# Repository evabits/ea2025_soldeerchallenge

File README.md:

# ea2025_soldeerchallenge

Hardware and Software for the soldering challenge of the Electronics and Automation fair 2025. The board includes an RP2040, a 5x5 neopixel LED array and a breakout connector. You can use it as an RP2040 development kit afterwards, starting with the Arduino file. Leave a note on our linkedin-page on how you've done. Good luck soldering!

## Important Notice  

Some Arduino board libraries may cause **GPIO pattern mismatches**.  

The only supported and correct board for running `FHI_SolderChallenge2025.ino` is:  

**Raspberry Pi Pico (RP2040) by Earle F. Philhower**

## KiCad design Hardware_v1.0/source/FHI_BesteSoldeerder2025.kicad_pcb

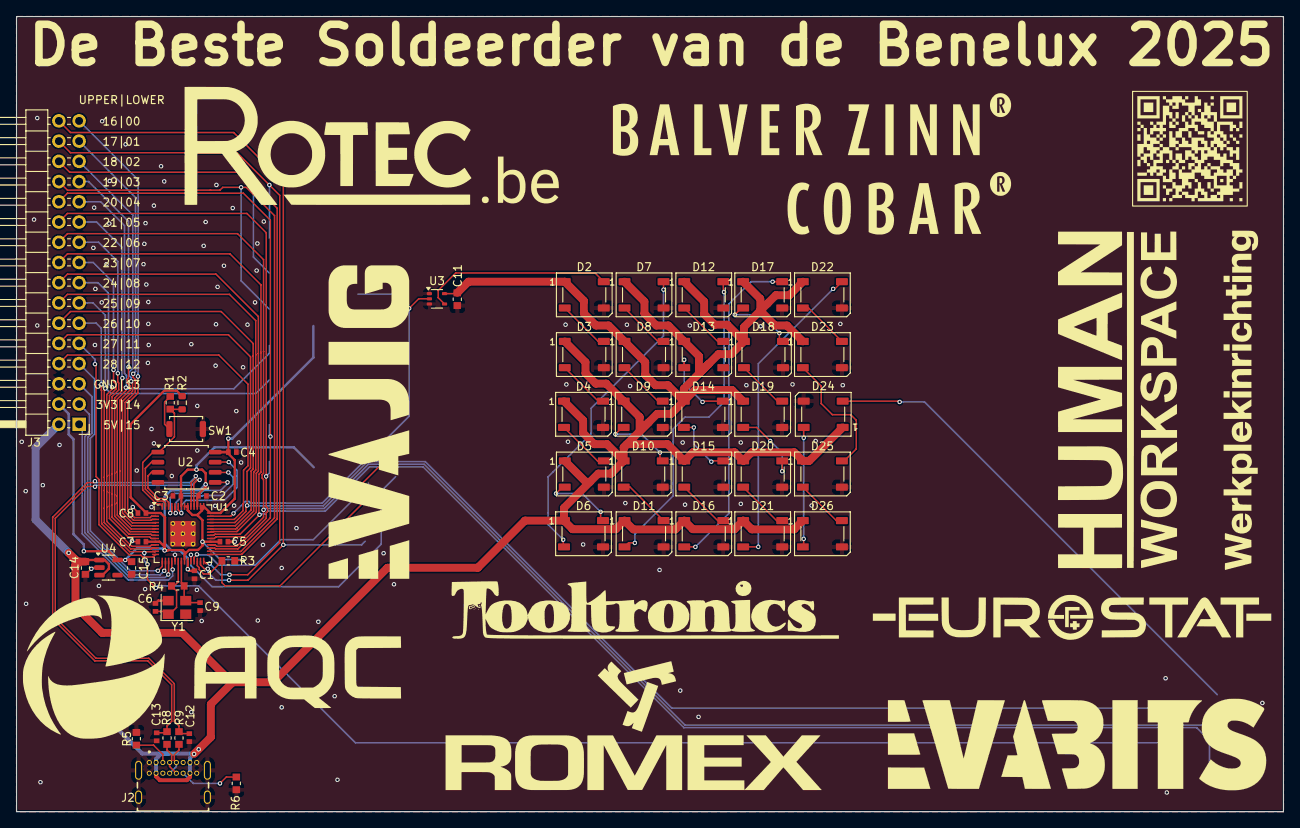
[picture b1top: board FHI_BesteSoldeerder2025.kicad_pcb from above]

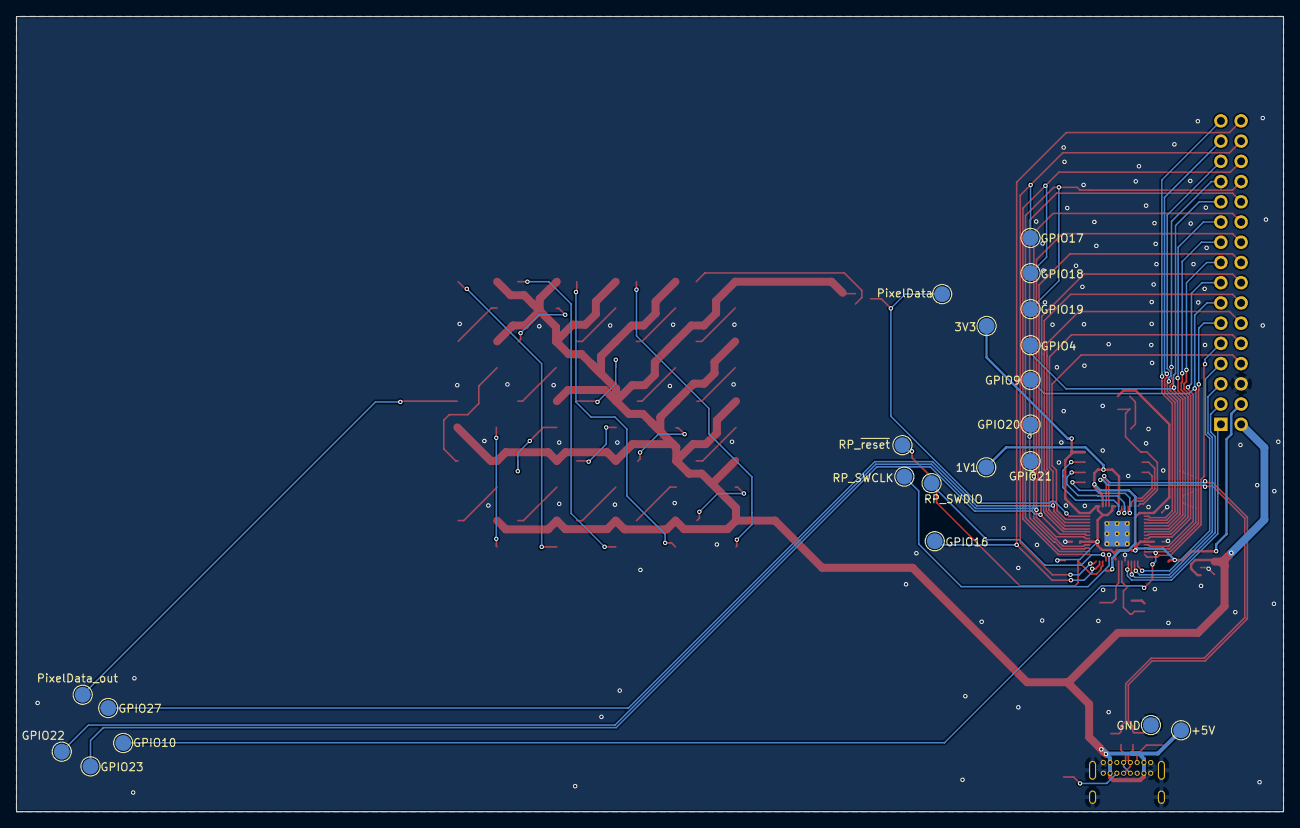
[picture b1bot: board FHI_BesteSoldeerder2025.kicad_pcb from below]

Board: 2 copper layers, 159.1 x 99.8 mm, 79 parts (21 on the bottom side), 78 nets.

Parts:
C1, C2, C3, C4, C5, C7, C8: 0.1uF; C_0402_1005Metric
C6, C9: 10pf; C_0402_1005Metric
C11, C14, C15: 1uF; C_0603_1608Metric
C12, C13: 22pF; C_0402_1005Metric
D2, D3, D4, D5, D6, D7, D8, D9, D10, D11, D12, D13, D14, D15, D16, D17, D18, D19, D20, D21, D22, D23, D24, D25, D26: WS2812B; LED_WS2812B_PLCC4_5.0x5.0mm_P3.2mm
J2: USB4085-GF-A_REVB; GCT_USB4085-GF-A_REVB
J3: Conn_02x16_Odd_Even; PinHeader_2x16_P2.54mm_Horizontal
R1: 1k5; R_0603_1608Metric
R2: DNP; R_0603_1608Metric
R3: 10K; R_0603_1608Metric
R4: 1M; R_0603_1608Metric
R5, R6: 5k1; R_0603_1608Metric
R8, R9: 27R; R_0603_1608Metric
SW1: SKRKAGE020; SW_Push_SPST_NO_Alps_SKRK
TP1: +5V; TestPoint_Pad_D1.5mm
TP3: GND; TestPoint_Pad_D1.5mm
TP28: GPIO27; TestPoint_Pad_D1.5mm
TP29: PixelData_out; TestPoint_Pad_D1.5mm
TP31: GPIO10; TestPoint_Pad_D1.5mm
TP32: GPIO22; TestPoint_Pad_D1.5mm
TP33: GPIO23; TestPoint_Pad_D1.5mm
TP55: GPIO21; TestPoint_Pad_D1.5mm
TP56: GPIO20; TestPoint_Pad_D1.5mm
TP57: GPIO9; TestPoint_Pad_D1.5mm
TP59: GPIO4; TestPoint_Pad_D1.5mm
TP60: GPIO19; TestPoint_Pad_D1.5mm
TP61: GPIO18; TestPoint_Pad_D1.5mm
TP62: GPIO17; TestPoint_Pad_D1.5mm
TP63: 1V1; TestPoint_Pad_D1.5mm
TP64: 3V3; TestPoint_Pad_D1.5mm
TP74: RP_SWDIO; TestPoint_Pad_D1.5mm
TP75: RP_~{reset}; TestPoint_Pad_D1.5mm
TP76: RP_SWCLK; TestPoint_Pad_D1.5mm
TP83: GPIO16; TestPoint_Pad_D1.5mm
TP84: PixelData; TestPoint_Pad_D1.5mm
U1: RP2040; QFN-56-1EP_7x7mm_P0.4mm_EP3.1x3.1mm_ThermalVias
U2: W25Q128JVSIQ; SOIC-8_5.23x5.23mm_P1.27mm
U3: 74HCT1G125GW; SOT-353_SC-70-5
U4: AP2112K-3.3V; TSOT-23-5
V1: QR-code; QRcode14mmx14mm
V2: EVAbits_logo; EVAbits_newlogo 48x12mm
V3: evajig_logo; evajig_logo_40x10
Y1: 12MHz,10pF; Crystal_SMD_3225-4Pin_3.2x2.5mm

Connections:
+3V3: C4.2, C5.2, C7.2, C8.2, C15.2, J3.4, R2.1, R3.2, TP64.1, U1.1 (IOVDD), U1.10 (IOVDD), U1.22 (IOVDD), U1.33 (IOVDD), U1.42 (IOVDD), U1.43 (ADC-AVDD), U1.44 (VREG-VIN), U1.48 (USB-VDD), U1.49 (IOVDD), U2.8 (VCC), U4.5 (OUT)
+5V: C11.2, C14.2, D2.1 (VDD), D3.1 (VDD), D4.1 (VDD), D5.1 (VDD), D6.1 (VDD), D7.1 (VDD), D8.1 (VDD), D9.1 (VDD), D10.1 (VDD), D11.1 (VDD), D12.1 (VDD), D13.1 (VDD), D14.1 (VDD), D15.1 (VDD), D16.1 (VDD), D17.1 (VDD), D18.1 (VDD), D19.1 (VDD), D20.1 (VDD), D21.1 (VDD), D22.1 (VDD), D23.1 (VDD), D24.1 (VDD), D25.1 (VDD), D26.1 (VDD), J2.A4 (VBUS), J2.A9 (VBUS), J2.B4 (VBUS), J2.B9 (VBUS), J3.2, TP1.1, U3.5 (Vcc), U4.1 (IN), U4.3 (EN)
/+1v1: C1.2, C2.2, C3.2, TP63.1, U1.23 (DVDD), U1.45 (VREG-VOUT), U1.50 (DVDD)
/GPIO00: J3.31, U1.2 (GPIO0)
/GPIO01: J3.29, U1.3 (GPIO1)
/GPIO02: J3.27, U1.4 (GPIO2)
/GPIO03: J3.25, U1.5 (GPIO3)
/GPIO04: J3.23, TP59.1, U1.6 (GPIO4)
/GPIO05: J3.21, U1.7 (GPIO5)
/GPIO06: J3.19, U1.8 (GPIO6)
/GPIO07: J3.17, U1.9 (GPIO7)
/GPIO08: J3.15, U1.11 (GPIO8)
/GPIO09: J3.13, TP57.1, U1.12 (GPIO9)
/GPIO10: J3.11, TP31.1, U1.13 (GPIO10)
/GPIO11: J3.9, U1.14 (GPIO11)
/GPIO12: J3.7, U1.15 (GPIO12)
/GPIO13: J3.5, U1.16 (GPIO13)
/GPIO14: J3.3, U1.17 (GPIO14)
/GPIO15: J3.1, U1.18 (GPIO15)
/GPIO16: J3.32, TP83.1, U1.27 (GPIO16)
/GPIO17: J3.30, TP62.1, U1.28 (GPIO17)
/GPIO18: J3.28, TP61.1, U1.29 (GPIO18)
/GPIO19: J3.26, TP60.1, U1.30 (GPIO19)
/GPIO20: J3.24, TP56.1, U1.31 (GPIO20)
/GPIO21: J3.22, TP55.1, U1.32 (GPIO21)
/GPIO22: J3.20, TP32.1, U1.34 (GPIO22)
/GPIO23: J3.18, TP33.1, U1.35 (GPIO23)
/GPIO24: J3.16, U1.36 (GPIO24)
/GPIO25: J3.14, U1.37 (GPIO25)
/GPIO26: J3.12, U1.38 (GPIO26/ADC0)
/GPIO27: J3.10, TP28.1, U1.39 (GPIO27/ADC1)
/GPIO28: J3.8, U1.40 (GPIO28/ADC2)
/NeoPixel_data: TP84.1, U1.41 (GPIO29/ADC3), U3.2 (A)
/NeoPixel_data_out: D24.2 (DOUT), TP29.1
/PICO_RESET: R3.1, TP75.1, U1.26 (RUN)
/PICO_TCKS: TP76.1, U1.24 (SWCLK)
/PICO_TMSS: TP74.1, U1.25 (SWDIO)
/QSPI_SCLK: U1.52 (QSPI-SCLK), U2.6 (CLK)
/QSPI_SD0: U1.53 (QSPI-SD0), U2.5 (DI(IO0))
/QSPI_SD1: U1.55 (QSPI-SD1), U2.2 (DO(IO1))
/QSPI_SD2: U1.54 (QSPI-SD2), U2.3 (IO2)
/QSPI_SD3: U1.51 (QSPI-SD3), U2.7 (IO3)
/QSPI_SS: R1.2, R2.2, U1.56 (QSPI-SS-N), U2.1 (~CS)
/USB_D+: C13.2, R8.1, U1.47 (USB-DP)
/USB_D-: C12.1, R9.1, U1.46 (USB-DM)
/USB_N: J2.A7 (DN1), J2.B7 (DN2), R9.2
/USB_P: J2.A6 (DP1), J2.B6 (DP2), R8.2
/~USB_BOOT: R1.1, SW1.2
GND: C1.1, C2.1, C3.1, C4.1, C5.1, C6.2, C7.1, C8.1, C9.1, C11.1, C12.2, C13.1, C14.1, C15.1, D2.3 (VSS), D3.3 (VSS), D4.3 (VSS), D5.3 (VSS), D6.3 (VSS), D7.3 (VSS), D8.3 (VSS), D9.3 (VSS), D10.3 (VSS), D11.3 (VSS), D12.3 (VSS), D13.3 (VSS), D14.3 (VSS), D15.3 (VSS), D16.3 (VSS), D17.3 (VSS), D18.3 (VSS), D19.3 (VSS), D20.3 (VSS), D21.3 (VSS), D22.3 (VSS), D23.3 (VSS), D24.3 (VSS), D25.3 (VSS), D26.3 (VSS), J2.A1 (GND), J2.A12 (GND), J2.B1 (GND), J2.B12 (GND), J2.S1 (SHELL), J2.S2 (SHELL), J2.S3 (SHELL), J2.S4 (SHELL), J3.6, R5.2, R6.2, SW1.1, TP3.1, U1.19 (TESTEN), U1.57 (GND), U2.4 (GND), U3.1 (~OE), U3.3 (GND), U4.2 (GND), Y1.2, Y1.4
unnamed: D2.4 (DIN), U3.4 (Y)
unnamed: D2.2 (DOUT), D3.4 (DIN)
unnamed: D3.2 (DOUT), D4.4 (DIN)
unnamed: D4.2 (DOUT), D5.4 (DIN)
unnamed: D5.2 (DOUT), D6.4 (DIN)
unnamed: D6.2 (DOUT), D7.4 (DIN)
unnamed: D7.2 (DOUT), D8.4 (DIN)
unnamed: D8.2 (DOUT), D9.4 (DIN)
unnamed: D9.2 (DOUT), D10.4 (DIN)
unnamed: D10.2 (DOUT), D11.4 (DIN)
unnamed: D11.2 (DOUT), D12.4 (DIN)
unnamed: D12.2 (DOUT), D13.4 (DIN)
unnamed: D13.2 (DOUT), D14.4 (DIN)
unnamed: D14.2 (DOUT), D15.4 (DIN)
unnamed: D15.2 (DOUT), D16.4 (DIN)
unnamed: D16.2 (DOUT), D17.4 (DIN)
unnamed: D17.2 (DOUT), D18.4 (DIN)
unnamed: D18.2 (DOUT), D19.4 (DIN)
unnamed: D19.2 (DOUT), D20.4 (DIN)
unnamed: D20.2 (DOUT), D21.4 (DIN)
unnamed: D21.2 (DOUT), D22.4 (DIN)
unnamed: D22.2 (DOUT), D23.4 (DIN)
unnamed: D23.2 (DOUT), D25.4 (DIN)
unnamed: D24.4 (DIN), D26.2 (DOUT)
unnamed: D25.2 (DOUT), D26.4 (DIN)
unnamed: J2.A5 (CC1), R5.1
unnamed: J2.B5 (CC2), R6.1
unnamed: C6.1, R4.2, U1.20 (XIN), Y1.1
unnamed: C9.2, R4.1, U1.21 (XOUT), Y1.3

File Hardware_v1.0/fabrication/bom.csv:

Value,References,Footprint,Partnumber,Quantity Per PCB,Description
10pf,C6 C9,C_0402_1005Metric,,2,
22pF,C12 C13,C_0402_1005Metric,,2,
0.1uF,C1 C2 C3 C4 C5 C7 C8,C_0402_1005Metric,,7,
1uF,C11 C14 C15,C_0603_1608Metric,,3,
WS2812B,D2 D3 D4 D5 D6 D7 D8 D9 D10 D11 D12 D13 D14 D15 D16 D17 D18 D19 D20 D21 D22 D23 D24 D25 D26,LED_WS2812B_PLCC4_5.0x5.0mm_P3.2mm,,25,RGB LED with integrated controller
Conn_02x16_Odd_Even,J3,PinHeader_2x16_P2.54mm_Horizontal,,1,"Generic connector, double row, 02x16, odd/even pin numbering scheme (row 1 odd numbers, row 2 even numbers), script generated (kicad-library-utils/schlib/autogen/connector/)"
USB4085-GF-A_REVB,J2,GCT_USB4085-GF-A_REVB,USB4085-GF-A,1,
27R,R8 R9,R_0603_1608Metric,,2,
1k5,R1,R_0603_1608Metric,,1,
5k1,R5 R6,R_0603_1608Metric,,2,
10K,R3,R_0603_1608Metric,,1,
1M,R4,R_0603_1608Metric,,1,
SKRKAGE020,SW1,SW_Push_SPST_NO_Alps_SKRK,SKRKAGE020,1,
74HCT1G125GW,U3,SOT-353_SC-70-5,,1,
AP2112K-3.3V,U4,TSOT-23-5,,1,
RP2040,U1,QFN-56-1EP_7x7mm_P0.4mm_EP3.1x3.1mm_ThermalVias,,1,
W25Q128JVSIQ,U2,SOIC-8_5.23x5.23mm_P1.27mm,,1,
EVAbits_logo,V2,EVAbits_newlogo 48x12mm,DNP,1,
QR-code,V1,QRcode14mmx14mm,DNP,1,
evajig_logo,V3,evajig_logo_40x10,DNP,1,
"12MHz,10pF",Y1,Crystal_SMD_3225-4Pin_3.2x2.5mm,NX3225SA-12MHZ-STD-CSR-6,1,

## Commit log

2025-09-15 for public
2025-09-16 removed unused BoMlines, updated iBOM
2025-09-17 removed more useless BoMlines, updated iBOM

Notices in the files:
parts and their libraries:
License: CC BY 4.0
